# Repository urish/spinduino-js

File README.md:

# spinduino.js

BLE PoV Fidget Spinner

Copyright (C) 2017, Uri Shaked

[Hackaday project page](https://hackaday.io/project/27220/)

## Features

* JavaScript programmable 
* 10-Pixel RGB PoV display (using APA102 LEDs) 
* Spin count / speed detection using a magnetic latch 
* Bluetooth Low Energy (BLE) communication with smart phone / computer for controlling the display, reading the spin count and programming 
* Over-the-air firmware upgrades 
* Fully open-source

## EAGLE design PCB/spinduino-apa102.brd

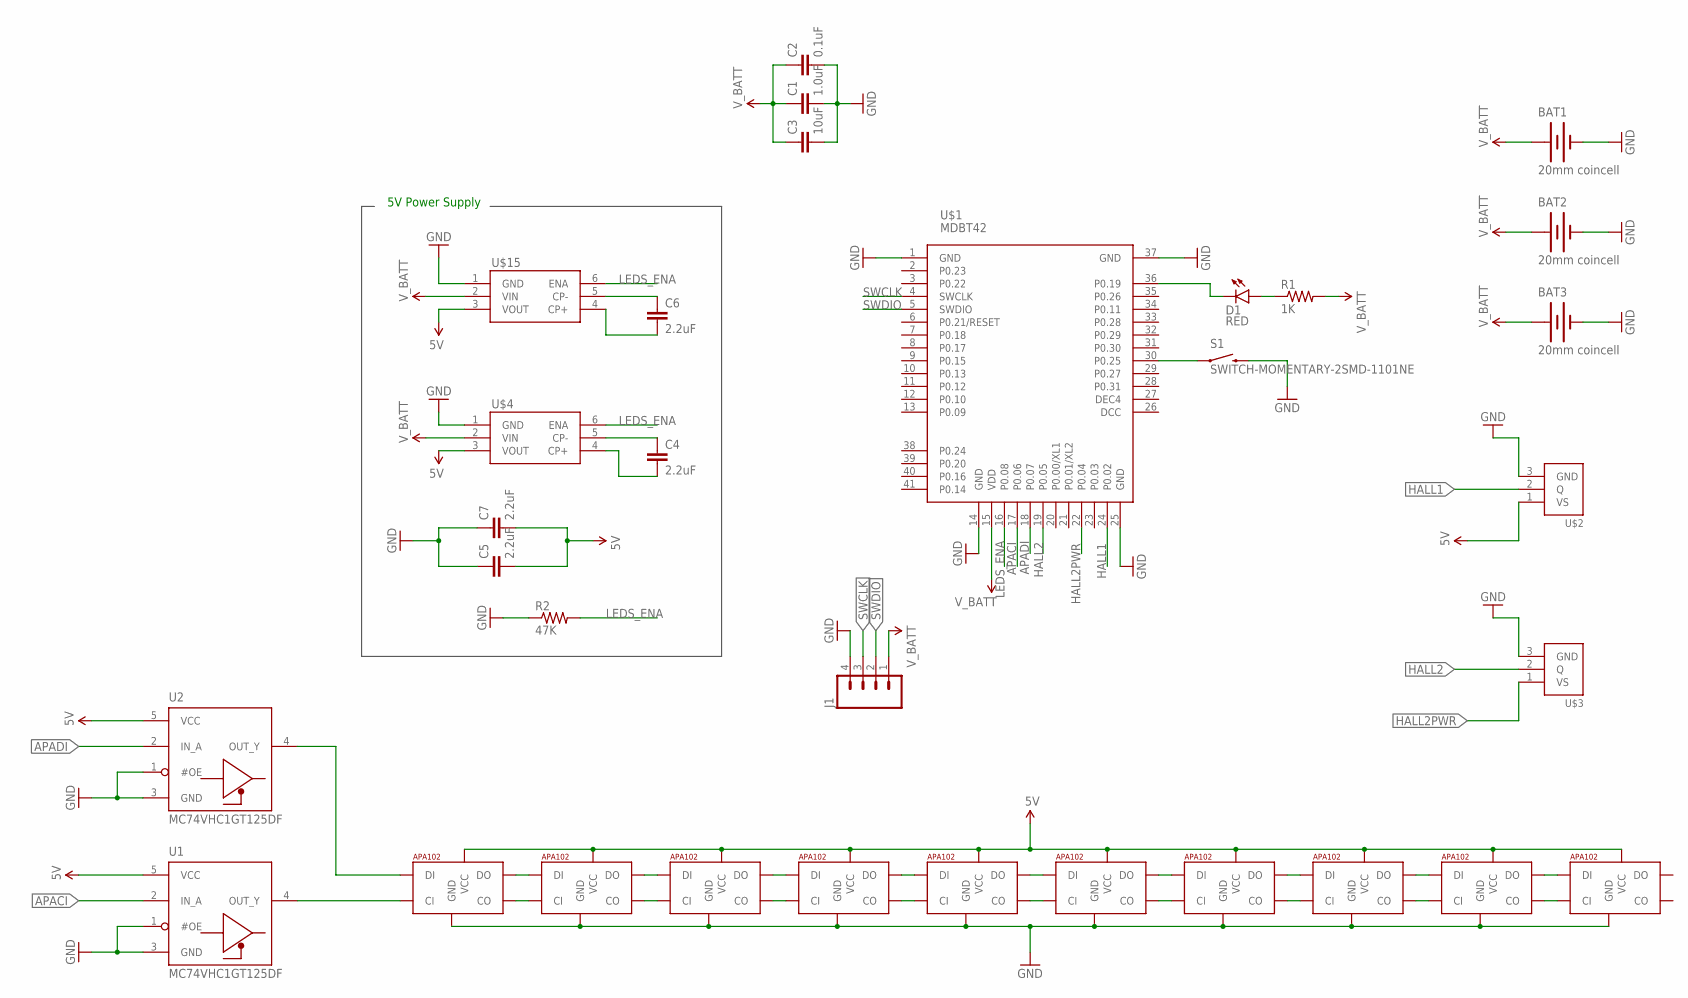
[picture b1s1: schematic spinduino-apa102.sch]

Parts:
BAT1, BAT2, BAT3: 20mm coincell; BATTCON_20MM_4LEGS
C1: 1.0uF; 0603-CAP
C2: 0.1uF; 0603-CAP
C3: 10uF; 0603-CAP
C4, C5, C6, C7: 2.2uF; 0603-CAP
D1: RED; LED-0603
J1: M04LOCK; 1X04_LOCK
R1: 1K; 0603-RES
R2: 47K; 0603-RES
S1: SWITCH-MOMENTARY-2SMD-1101NE; TACTILE-SWITCH-1101NE
U1, U2: MC74VHC1GT125DF; SOT353
U$1: MDBT42
U$2, U$3: TLE4946-2KSMD; SC-59
U$4, U$15: TPS60150; WSON6
U$5, U$6, U$7, U$8, U$9, U$10, U$11, U$12, U$13, U$14: APA1022020; APA102_2020

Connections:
5V: C5.2, C7.2, U1.5 (VCC), U2.5 (VCC), U$2.1 (VS), U$4.3 (VOUT), U$5.V_CC (VCC), U$6.V_CC (VCC), U$7.V_CC (VCC), U$8.V_CC (VCC), U$9.V_CC (VCC), U$10.V_CC (VCC), U$11.V_CC (VCC), U$12.V_CC (VCC), U$13.V_CC (VCC), U$14.V_CC (VCC), U$15.3 (VOUT)
APACI: U1.2 (IN_A), U$1.17 (P0.06)
APADI: U2.2 (IN_A), U$1.18 (P0.07)
GND: BAT1.NEGATIVE (-), BAT2.NEGATIVE (-), BAT3.NEGATIVE (-), C1.2, C2.2, C3.2, C5.1, C7.1, J1.4, R2.1, S1.2, U1.1 (#OE), U1.3 (GND), U2.1 (#OE), U2.3 (GND), U$1.1 (GND), U$1.14 (GND), U$1.25 (GND), U$1.37 (GND), U$2.3 (GND), U$3.3 (GND), U$4.1 (GND), U$5.GND, U$6.GND, U$7.GND, U$8.GND, U$9.GND, U$10.GND, U$11.GND, U$12.GND, U$13.GND, U$14.GND, U$15.1 (GND)
HALL1: U$1.24 (P0.02), U$2.2 (Q)
HALL2: U$1.19 (P0.05), U$3.2 (Q)
HALL2PWR: U$1.22 (P0.04), U$3.1 (VS)
LEDS_ENA: R2.2, U$1.16 (P0.08), U$4.6 (ENA), U$15.6 (ENA)
unnamed: U$10.C_IN (CI), U$11.CL_OUT (CO)
unnamed: U$10.D_IN (DI), U$11.D_OUT (DO)
unnamed: D1.C, U$1.36 (P0.19)
unnamed: D1.A, R1.1
unnamed: U$5.D_IN (DI), U$6.D_OUT (DO)
unnamed: U$5.C_IN (CI), U$6.CL_OUT (CO)
unnamed: U$6.D_IN (DI), U$7.D_OUT (DO)
unnamed: U$6.C_IN (CI), U$7.CL_OUT (CO)
unnamed: U$7.D_IN (DI), U$8.D_OUT (DO)
unnamed: U$7.C_IN (CI), U$8.CL_OUT (CO)
unnamed: U$8.D_IN (DI), U$9.D_OUT (DO)
unnamed: U$8.C_IN (CI), U$9.CL_OUT (CO)
unnamed: U$9.D_IN (DI), U$10.D_OUT (DO)
unnamed: U$9.C_IN (CI), U$10.CL_OUT (CO)
unnamed: U$11.D_IN (DI), U$12.D_OUT (DO)
unnamed: U$11.C_IN (CI), U$12.CL_OUT (CO)
unnamed: U$12.D_IN (DI), U$13.D_OUT (DO)
unnamed: U$12.C_IN (CI), U$13.CL_OUT (CO)
unnamed: U$13.D_IN (DI), U$14.D_OUT (DO)
unnamed: U$13.C_IN (CI), U$14.CL_OUT (CO)
unnamed: S1.1, U$1.30 (P0.25)
unnamed: C4.2, U$4.4 (CP+)
unnamed: C4.1, U$4.5 (CP-)
unnamed: U2.4 (OUT_Y), U$14.D_IN (DI)
unnamed: U1.4 (OUT_Y), U$14.C_IN (CI)
unnamed: C6.1, U$15.5 (CP-)
unnamed: C6.2, U$15.4 (CP+)
SWCLK: J1.3, U$1.4 (SWCLK)
SWDIO: J1.2, U$1.5 (SWDIO)
V_BATT: BAT1.POSITIVE@1 (+), BAT1.POSITIVE@2 (+), BAT1.POSITIVE@3 (+), BAT1.POSITIVE@4 (+), BAT2.POSITIVE@1 (+), BAT2.POSITIVE@2 (+), BAT2.POSITIVE@3 (+), BAT2.POSITIVE@4 (+), BAT3.POSITIVE@1 (+), BAT3.POSITIVE@2 (+), BAT3.POSITIVE@3 (+), BAT3.POSITIVE@4 (+), C1.1, C2.1, C3.1, J1.1, R1.2, U$1.15 (VDD), U$4.2 (VIN), U$15.2 (VIN)

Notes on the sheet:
5V Power Supply

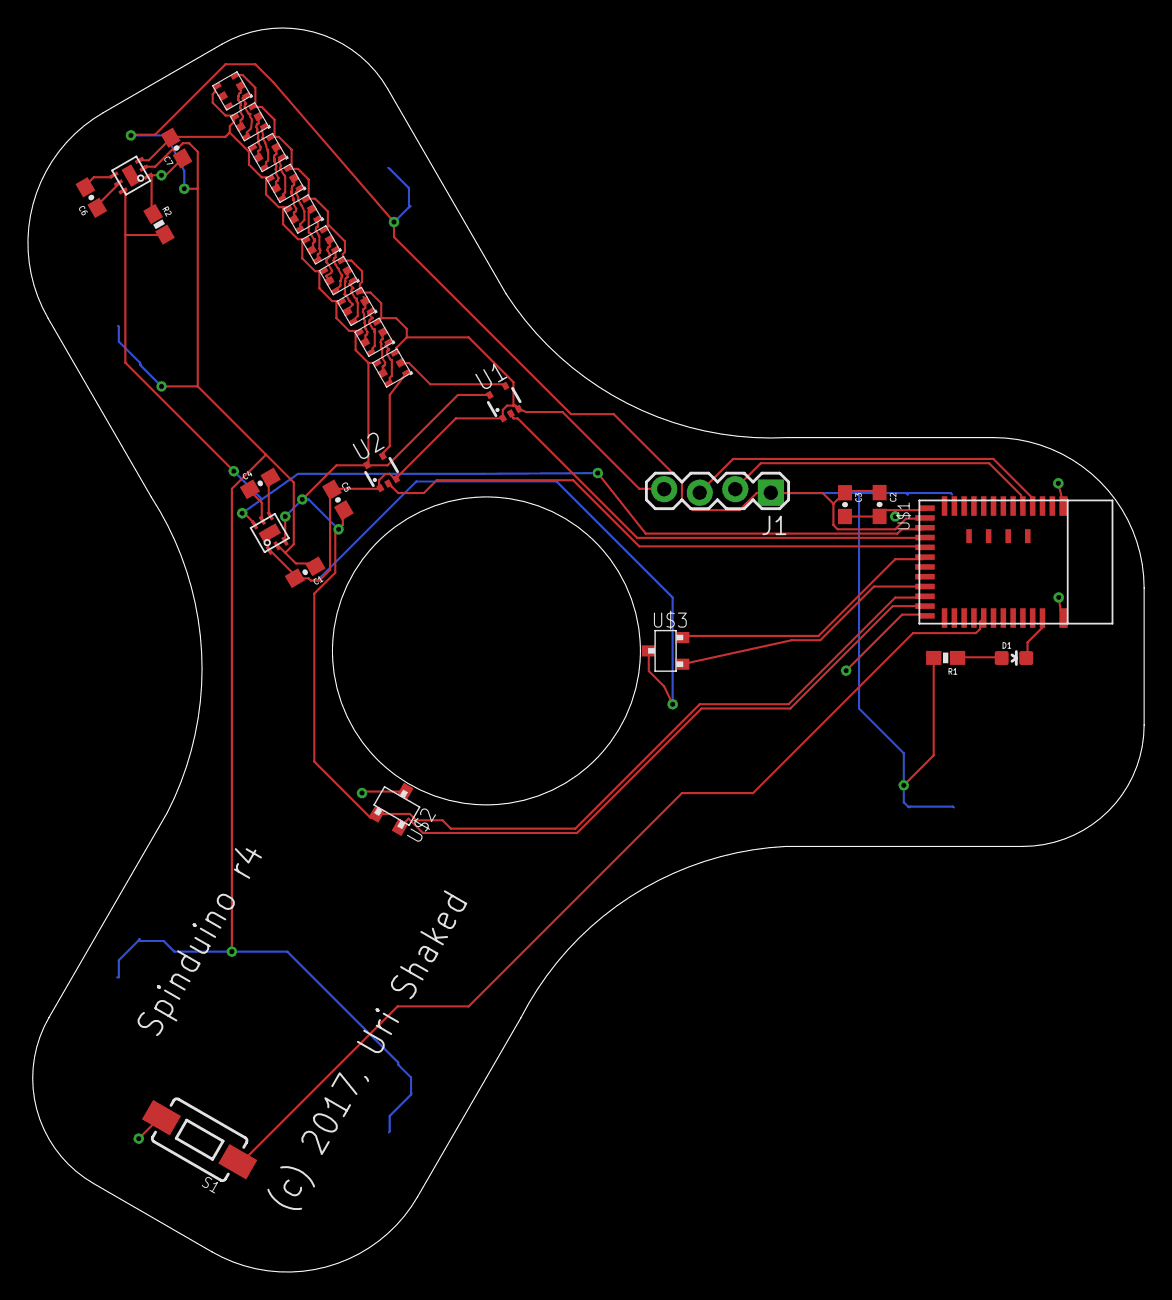
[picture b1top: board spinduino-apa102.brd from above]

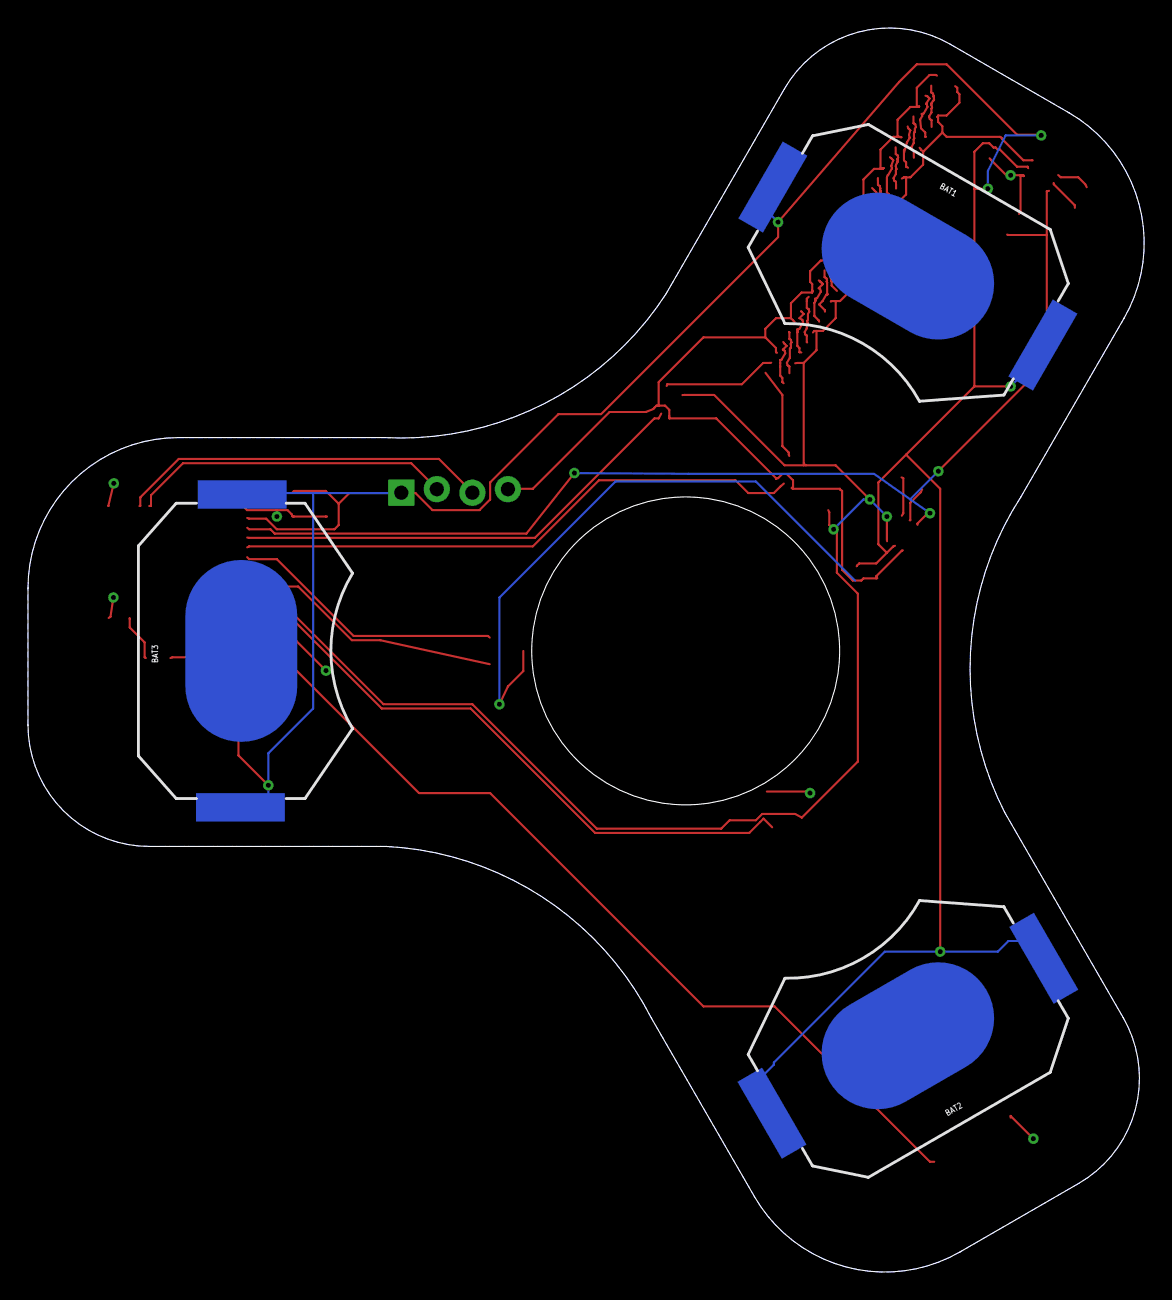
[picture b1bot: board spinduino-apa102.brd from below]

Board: 2 copper layers, 79.7 x 88.9 mm, 32 parts (3 on the bottom side), 38 nets.

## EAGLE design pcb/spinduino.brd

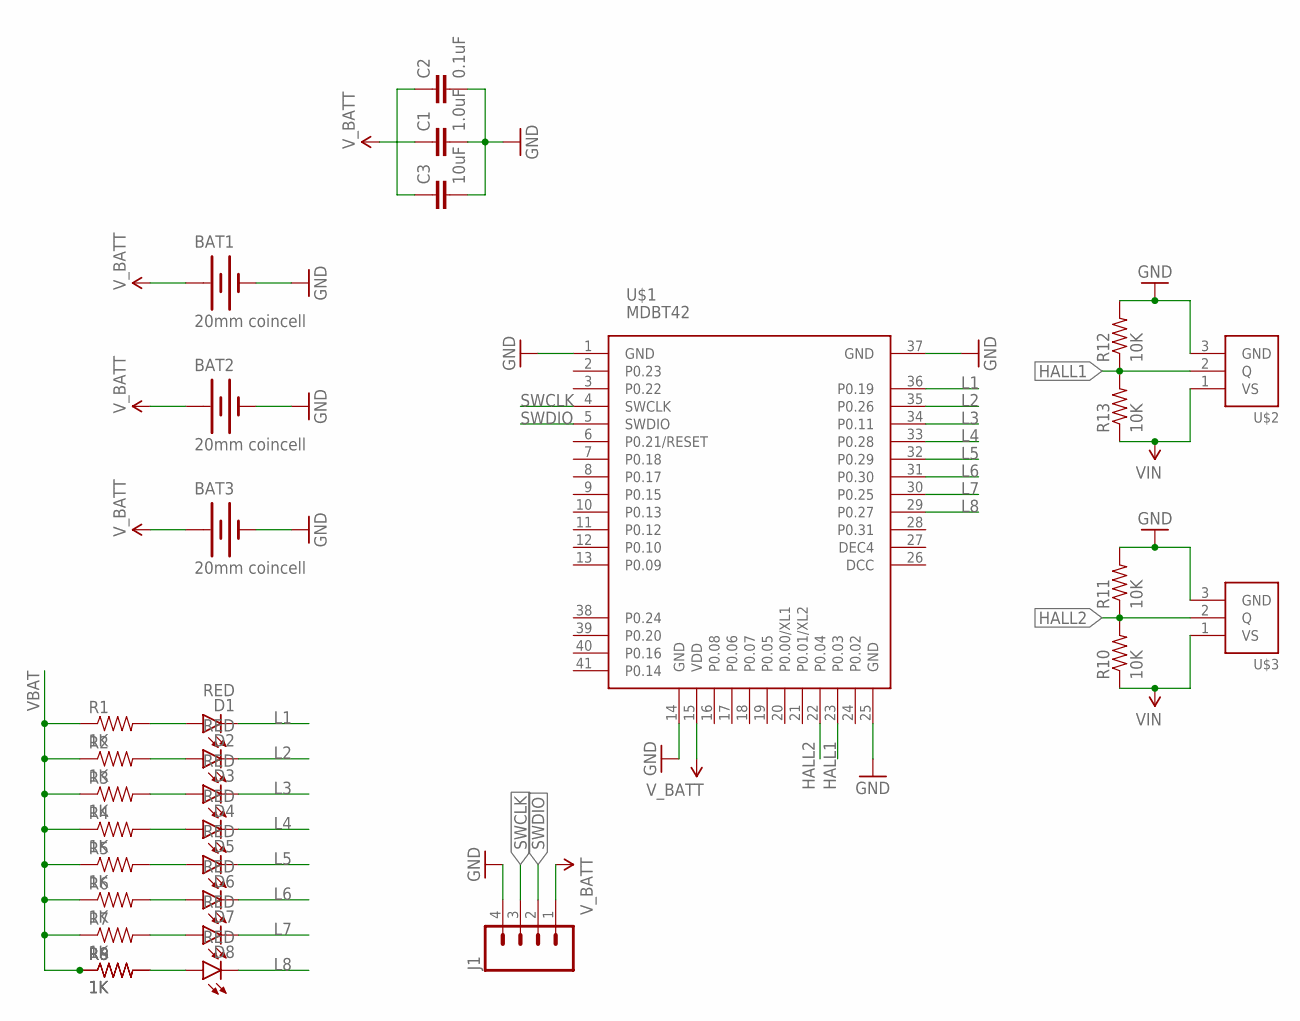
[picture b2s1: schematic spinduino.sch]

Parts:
BAT1, BAT2, BAT3: 20mm coincell; BATTCON_20MM_4LEGS
C1: 1.0uF; 0603-CAP
C2: 0.1uF; 0603-CAP
C3: 10uF; 0603-CAP
D1, D2, D3, D4, D5, D6, D7, D8: RED; LED-0603
J1: M04LOCK; 1X04_LOCK
R1, R2, R3, R4, R5, R6, R7, R8, R9: 1K; 0603-RES
R10, R11, R12, R13: 10K; 0603-RES
U$1: MDBT42
U$2, U$3: TLE4946-2KSMD; SC-59

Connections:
GND: BAT1.NEGATIVE (-), BAT2.NEGATIVE (-), BAT3.NEGATIVE (-), C1.2, C2.2, C3.2, J1.4, R11.2, R12.2, U$1.1 (GND), U$1.14 (GND), U$1.25 (GND), U$1.37 (GND), U$2.3 (GND), U$3.3 (GND)
HALL1: R12.1, R13.2, U$1.23 (P0.03), U$2.2 (Q)
HALL2: R10.2, R11.1, U$1.22 (P0.04), U$3.2 (Q)
L1: D1.C, U$1.36 (P0.19)
L2: D2.C, U$1.35 (P0.26)
L3: D3.C, U$1.34 (P0.11)
L4: D4.C, U$1.33 (P0.28)
L5: D5.C, U$1.32 (P0.29)
L6: D6.C, U$1.31 (P0.30)
L7: D7.C, U$1.30 (P0.25)
L8: D8.C, U$1.29 (P0.27)
unnamed: D8.A, R8.2, R9.2
unnamed: D1.A, R1.2
unnamed: D2.A, R2.2
unnamed: D3.A, R3.2
unnamed: D4.A, R4.2
unnamed: D5.A, R5.2
unnamed: D6.A, R6.2
unnamed: D7.A, R7.2
SWCLK: J1.3, U$1.4 (SWCLK)
SWDIO: J1.2, U$1.5 (SWDIO)
VBAT: R1.1, R2.1, R3.1, R4.1, R5.1, R6.1, R7.1, R8.1, R9.1, R10.1, R13.1, U$2.1 (VS), U$3.1 (VS)
V_BATT: BAT1.POSITIVE@1 (+), BAT1.POSITIVE@2 (+), BAT1.POSITIVE@3 (+), BAT1.POSITIVE@4 (+), BAT2.POSITIVE@1 (+), BAT2.POSITIVE@2 (+), BAT2.POSITIVE@3 (+), BAT2.POSITIVE@4 (+), BAT3.POSITIVE@1 (+), BAT3.POSITIVE@2 (+), BAT3.POSITIVE@3 (+), BAT3.POSITIVE@4 (+), C1.1, C2.1, C3.1, J1.1, U$1.15 (VDD)

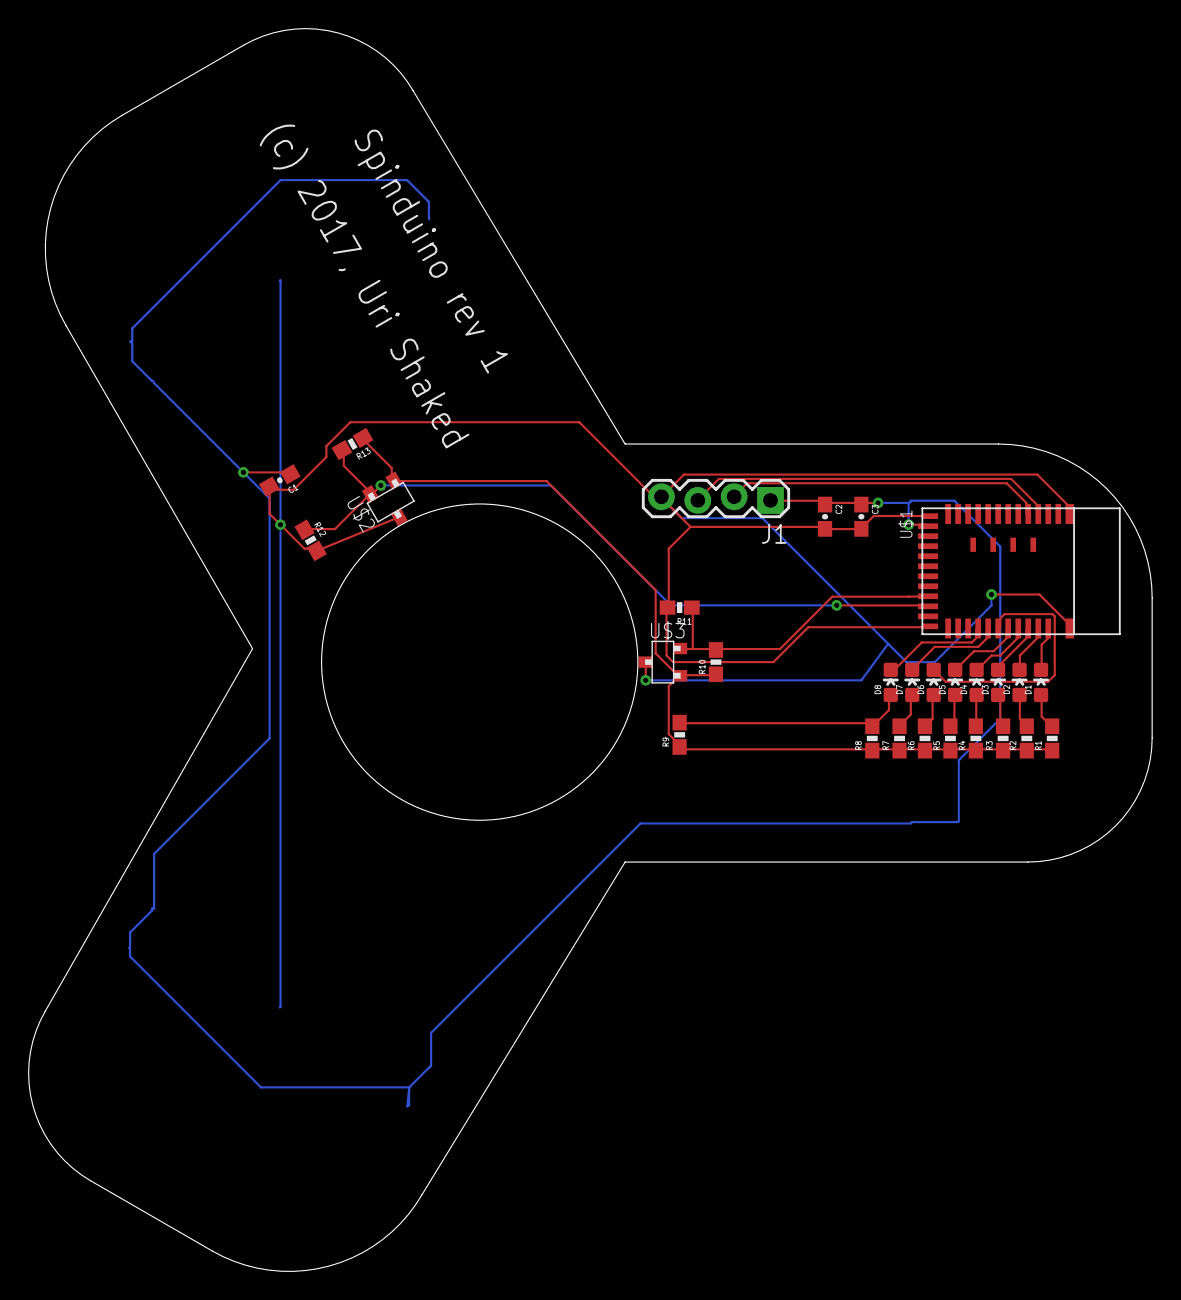
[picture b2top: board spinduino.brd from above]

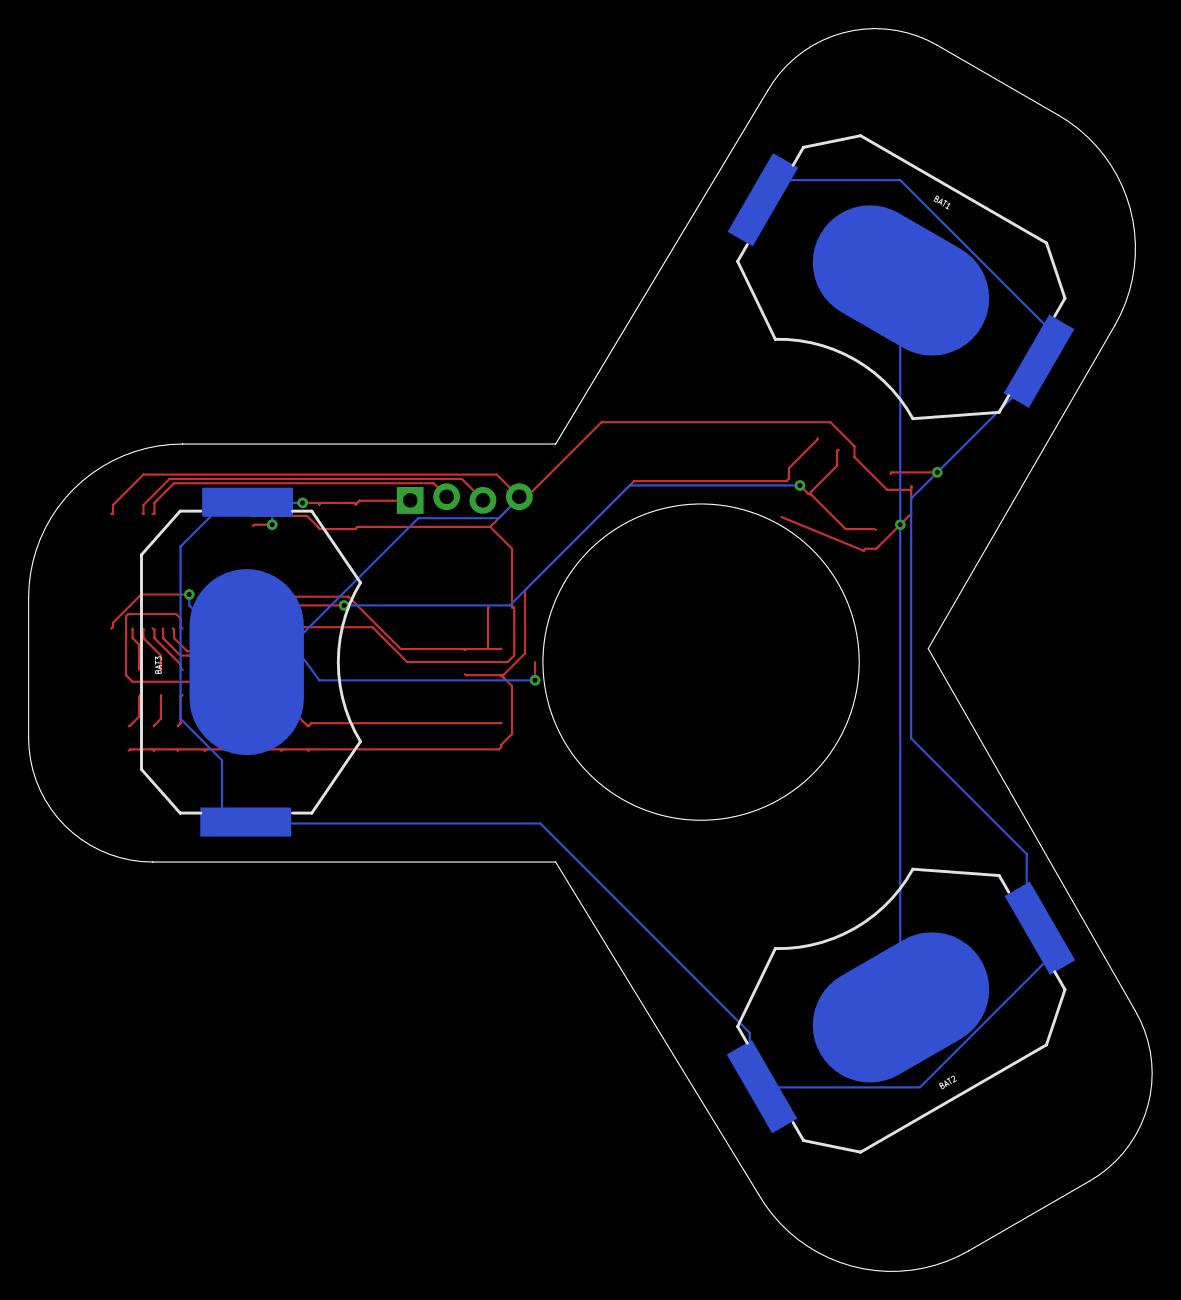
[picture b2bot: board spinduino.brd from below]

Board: 2 copper layers, 78.5 x 86.8 mm, 31 parts (3 on the bottom side), 23 nets.

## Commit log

2017-07-31 add programming connector
2017-08-01 add APA102-2020 variant
2017-08-01 add .gitignore
2017-08-23 add bearing cap scad file
2017-08-23 fix: remove redundant resistor
2017-09-08 Make hall effect sensors powered by CPU
    This will help with standby power consumption
2017-09-08 reduce inner hole diameter
2017-09-08 update board revision number
2017-09-09 fix: make spinner symetrical
2017-09-09 cleanup: remove old spinduino files
2017-09-09 feat: ground plane on bottom layer
2017-09-09 improve bearing cap
2017-09-09 feat: powed the LEDs by 5V pump
2017-09-09 fix: cover vias with solder mask
2017-09-09 doc: add README
2017-09-27 fix a few issues in board:
    1. remove copper under antenna
    2. fix wrong pin assignments of TPS60150
    3. shrink inner hole a bit
    4. fix package for MC74VHC1GT125 (SOT353 instead of SOT23-5)
    5. move text to a different wing
2017-10-01 fix: add pull-down resistor for the TPS60150 enable pin
2017-10-01 fix: update revision number (4)
2017-10-20 feat: Spinduino firmware with some initial patterns
2017-10-21 feat(firmware): migrate code to use new `spinner.stop()`
    the stop method clears all scheduled buffers
2017-10-24 feat: add bulb demo
2017-10-24 Glow beyond yellow, to white hot!
2017-10-25 feat: add Chrome Logo pattern
2017-10-25 fix(firmware): add cleanup code to bulb demo
2017-10-29 feat: initial PoV firmware
2017-10-29 fix: use D2 hall sensor instead of D5
2017-10-29 fix: Remove APA text from silk screen
2017-10-29 fix: connect one of the hall effect sensors to the 5v power supply
2017-11-01 fix: rotate the APA 102 LEDs
    So the red / green / blue are aligned (more or less)

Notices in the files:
parts and their libraries:
SparkFun-Resistors: Licensing: Creative Commons ShareAlike 4.0 International - https://creativecommons.org/licenses/by-sa/4.0
